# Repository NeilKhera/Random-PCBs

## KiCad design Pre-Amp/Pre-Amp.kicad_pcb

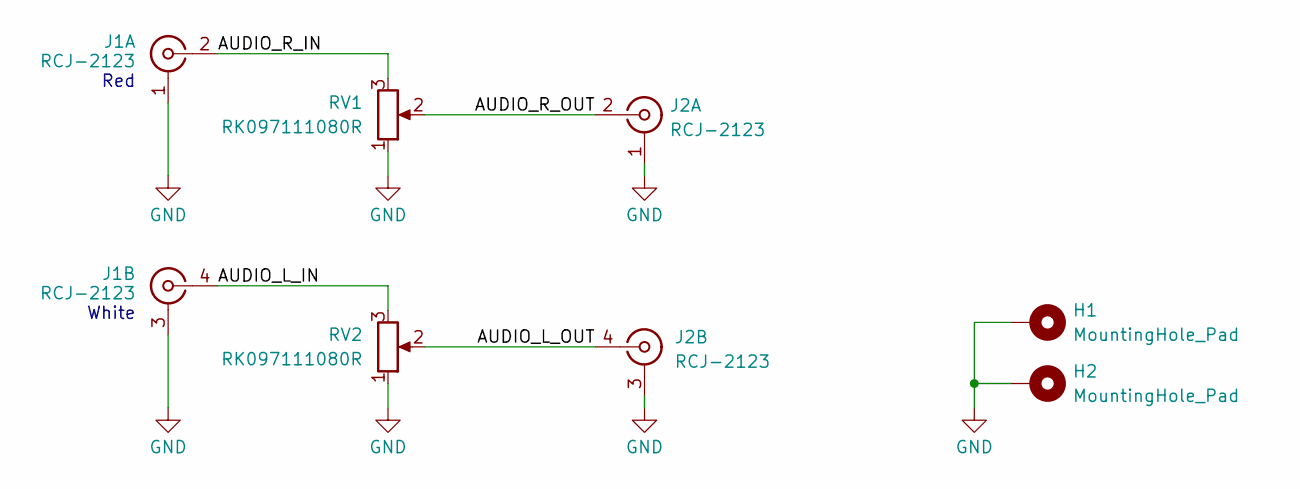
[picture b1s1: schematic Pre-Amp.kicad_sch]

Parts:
H1, H2: MountingHole_Pad; MountingHole_3.2mm_M3_DIN965_Pad
J1, J2: RCJ-2123; RCJ-2121
RV1, RV2: RK097111080R; Potentiometer_Alps_RK097_Single_Horizontal

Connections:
/AUDIO_L_IN: J1.4 (In2), RV2.3
/AUDIO_L_OUT: J2.4 (In2), RV2.2
/AUDIO_R_IN: J1.2 (In1), RV1.3
/AUDIO_R_OUT: J2.2 (In1), RV1.2
GND: H1.1, H2.1, J1.1 (Ext1), J1.3 (Ext2), J2.1 (Ext1), J2.3 (Ext2), RV1.1, RV2.1

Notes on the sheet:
Red
White

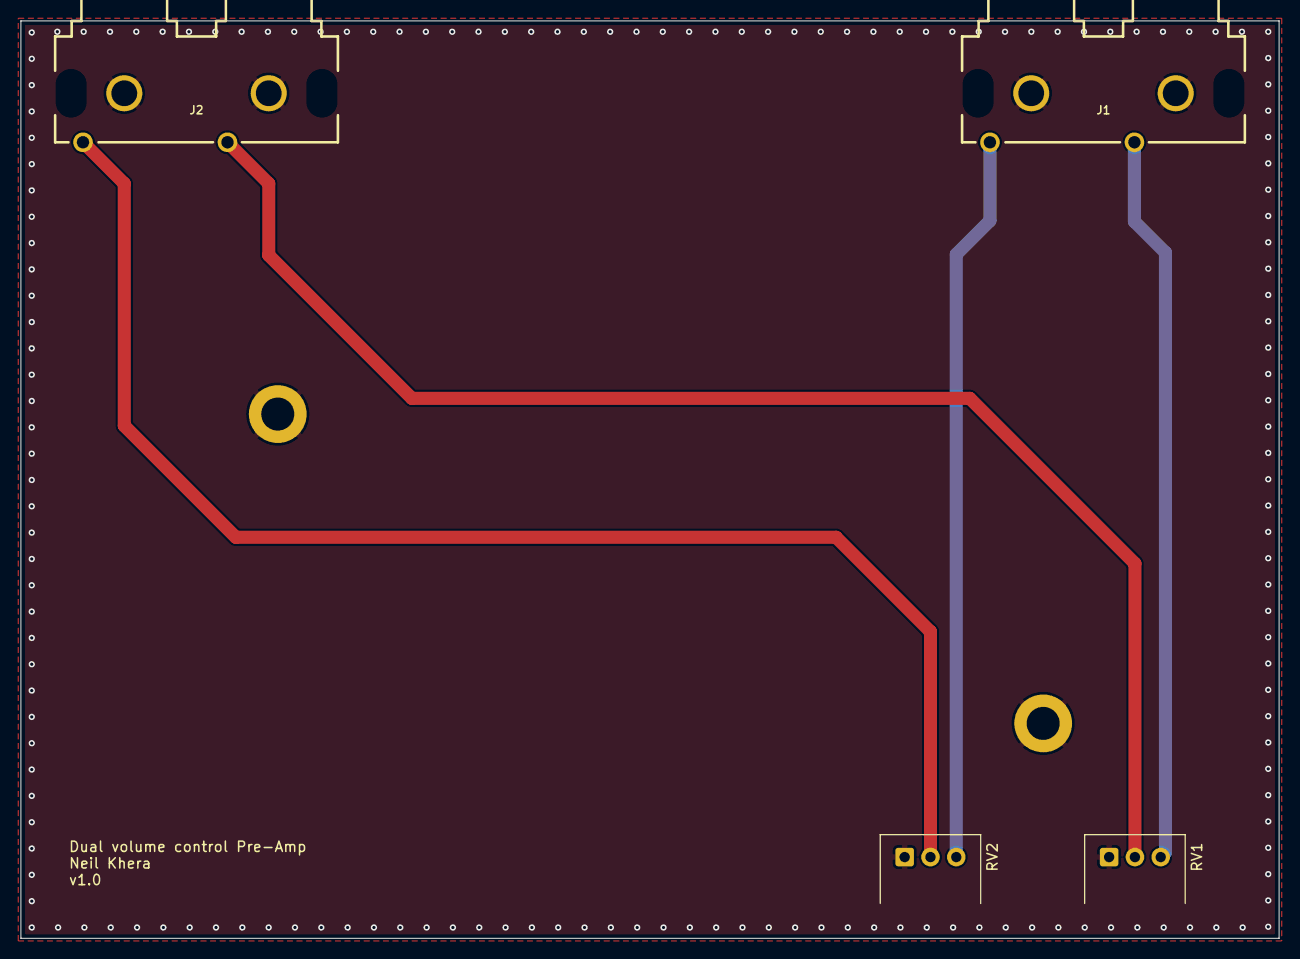
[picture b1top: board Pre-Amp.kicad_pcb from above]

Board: 2 copper layers, 121.9 x 88.9 mm, 6 parts (0 on the bottom side), 5 nets.

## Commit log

2026-04-19 Move files into folder
